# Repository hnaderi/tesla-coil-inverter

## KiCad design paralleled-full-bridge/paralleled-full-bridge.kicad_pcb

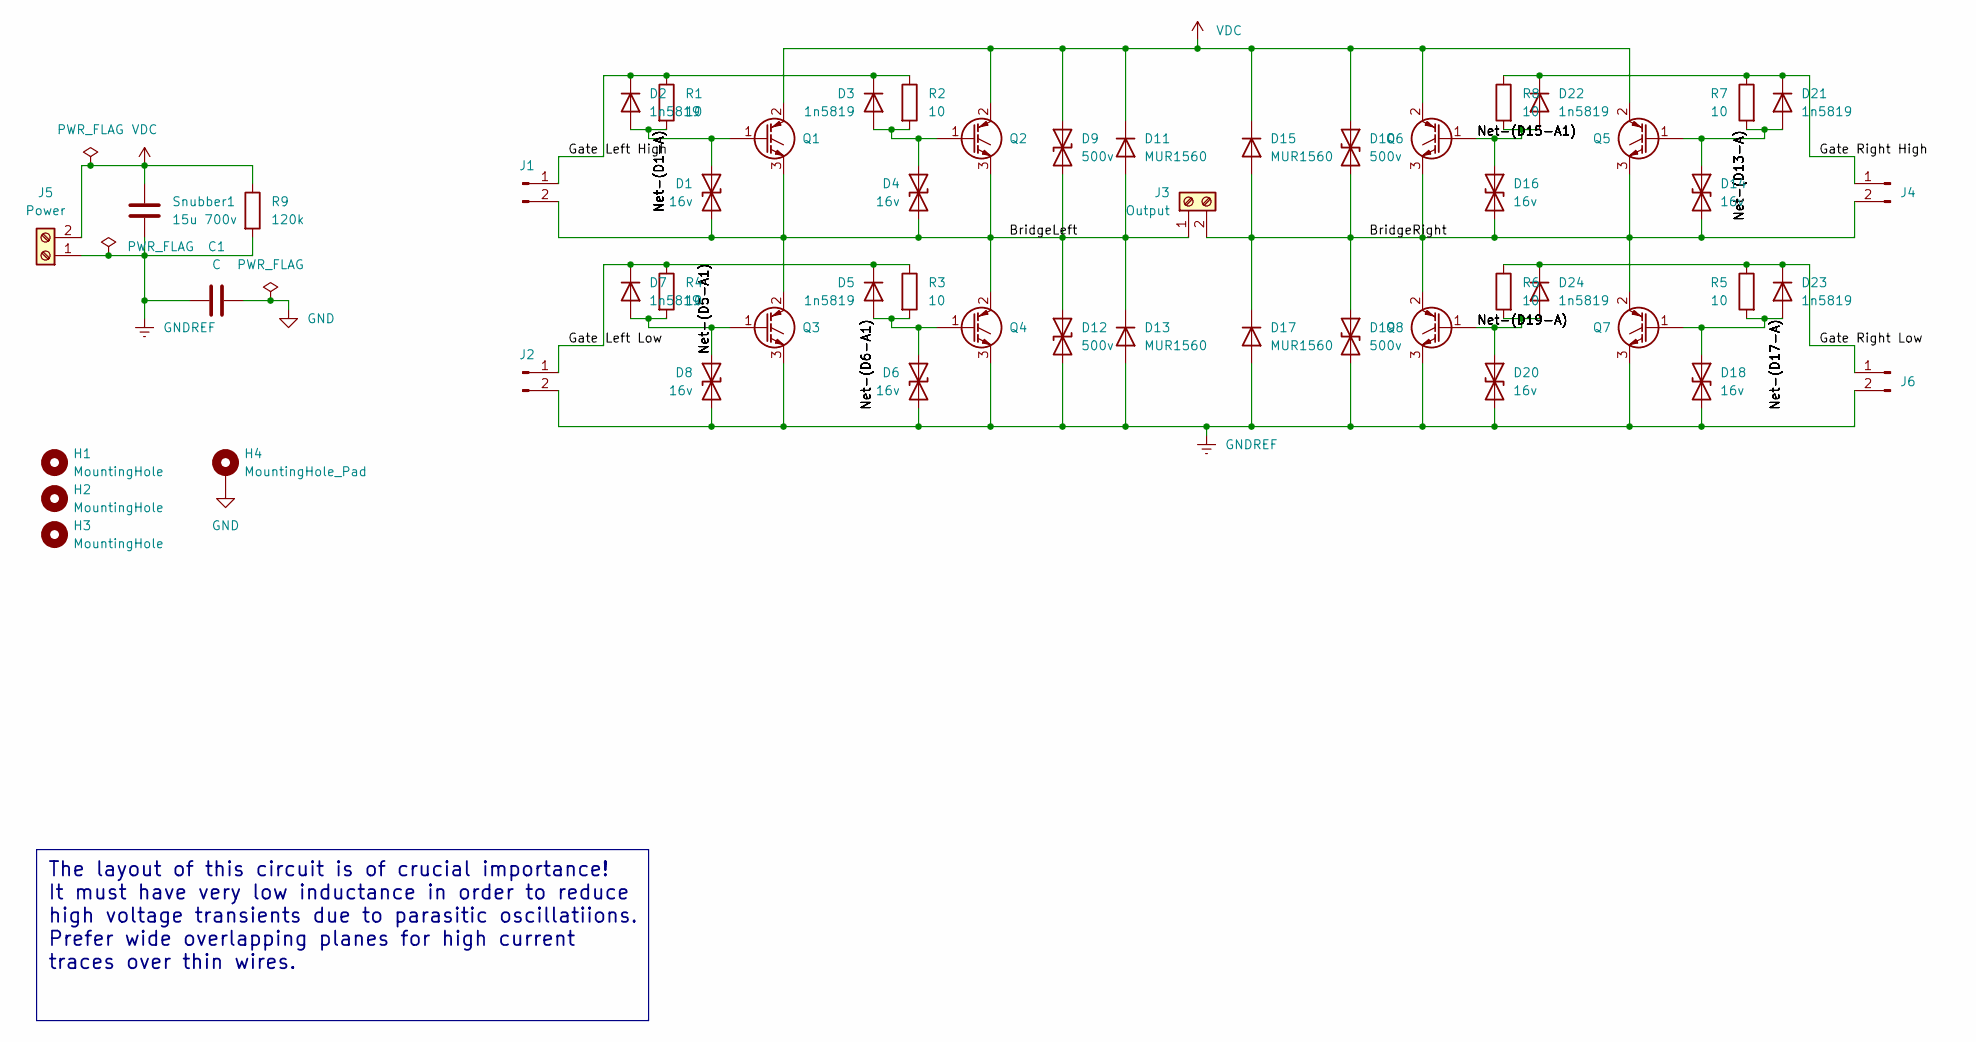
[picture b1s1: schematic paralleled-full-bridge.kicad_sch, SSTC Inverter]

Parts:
C1: C; C_Rect_L26.5mm_W5.0mm_P22.50mm_MKS4
D1, D4, D6, D8, D14, D16, D18, D20: 16v; D_DO-201_P3.81mm_Vertical_KathodeUp
D2, D3, D5, D7, D21, D22, D23, D24: 1n5819; D_DO-41_SOD81_P7.62mm_Horizontal
D9, D10, D12, D19: 500v; D_DO-15_P10.16mm_Horizontal
D11, D13, D15, D17: MUR1560; TO-220-2_Vertical
H1, H2, H3: MountingHole; MountingHole_3.2mm_M3
H4: MountingHole_Pad; MountingHole_3.2mm_M3_DIN965_Pad_TopBottom
J1, J2, J4, J6: Conn_01x02_Pin; JST_XH_B2B-XH-A_1x02_P2.50mm_Vertical
J3: Output; TerminalBlock_bornier-2_P5.08mm
J5: Power; TerminalBlock_bornier-2_P5.08mm
Q1, Q2, Q3, Q4, Q5, Q6, Q7, Q8: Q_NIGBT_GCE; TO-247-3_Vertical
R1, R2, R3, R4, R5, R6, R7, R8: 10; R_Axial_DIN0207_L6.3mm_D2.5mm_P7.62mm_Horizontal
R9: 120k; R_Axial_DIN0516_L15.5mm_D5.0mm_P20.32mm_Horizontal
Snubber1: 15u 700v; C_Rect_L41.5mm_W20.0mm_P37.50mm_MKS4

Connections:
/BridgeLeft: D1.2 (A2), D4.2 (A2), D9.2 (A2), D11.2 (A), D12.1 (A1), D13.1 (K), J1.2, J3.1, Q1.3 (E), Q2.3 (E), Q3.2 (C), Q4.2 (C)
/BridgeRight: D10.2 (A2), D14.2 (A2), D15.2 (A), D16.2 (A2), D17.1 (K), D19.1 (A1), J3.2, J4.2, Q5.3 (E), Q6.3 (E), Q7.2 (C), Q8.2 (C)
/Gate Left High: D2.1 (K), D3.1 (K), J1.1, R1.1, R2.1
/Gate Left Low: D5.1 (K), D7.1 (K), J2.1, R3.1, R4.1
/Gate Right High: D21.1 (K), D22.1 (K), J4.1, R7.1, R8.1
/Gate Right Low: D23.1 (K), D24.1 (K), J6.1, R5.1, R6.1
/Net-(D1-A): D1.1 (A1), D2.2 (A), Q1.1 (G), R1.2
/Net-(D5-A1): D7.2 (A), D8.1 (A1), Q3.1 (G), R4.2
/Net-(D6-A1): D5.2 (A), D6.1 (A1), Q4.1 (G), R3.2
/Net-(D13-A): D14.1 (A1), D21.2 (A), Q5.1 (G), R7.2
/Net-(D15-A1): D16.1 (A1), D22.2 (A), Q6.1 (G), R8.2
/Net-(D17-A): D18.1 (A1), D23.2 (A), Q7.1 (G), R5.2
/Net-(D19-A): D20.1 (A1), D24.2 (A), Q8.1 (G), R6.2
GND: C1.2, H4.1
GNDREF: C1.1, D6.2 (A2), D8.2 (A2), D12.2 (A2), D13.2 (A), D17.2 (A), D18.2 (A2), D19.2 (A2), D20.2 (A2), J2.2, J5.1, J6.2, Q3.3 (E), Q4.3 (E), Q7.3 (E), Q8.3 (E), R9.2, Snubber1.1
unnamed: D3.2 (A), D4.1 (A1), Q2.1 (G), R2.2
VDC: D9.1 (A1), D10.1 (A1), D11.1 (K), D15.1 (K), J5.2, Q1.2 (C), Q2.2 (C), Q5.2 (C), Q6.2 (C), R9.1, Snubber1.2

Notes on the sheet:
The layout of this circuit is of crucial importance! It must have very low inductance in order to reduce high voltage transients due to parasitic oscillatiions. Prefer wide overlapping planes for high current traces over thin wires.

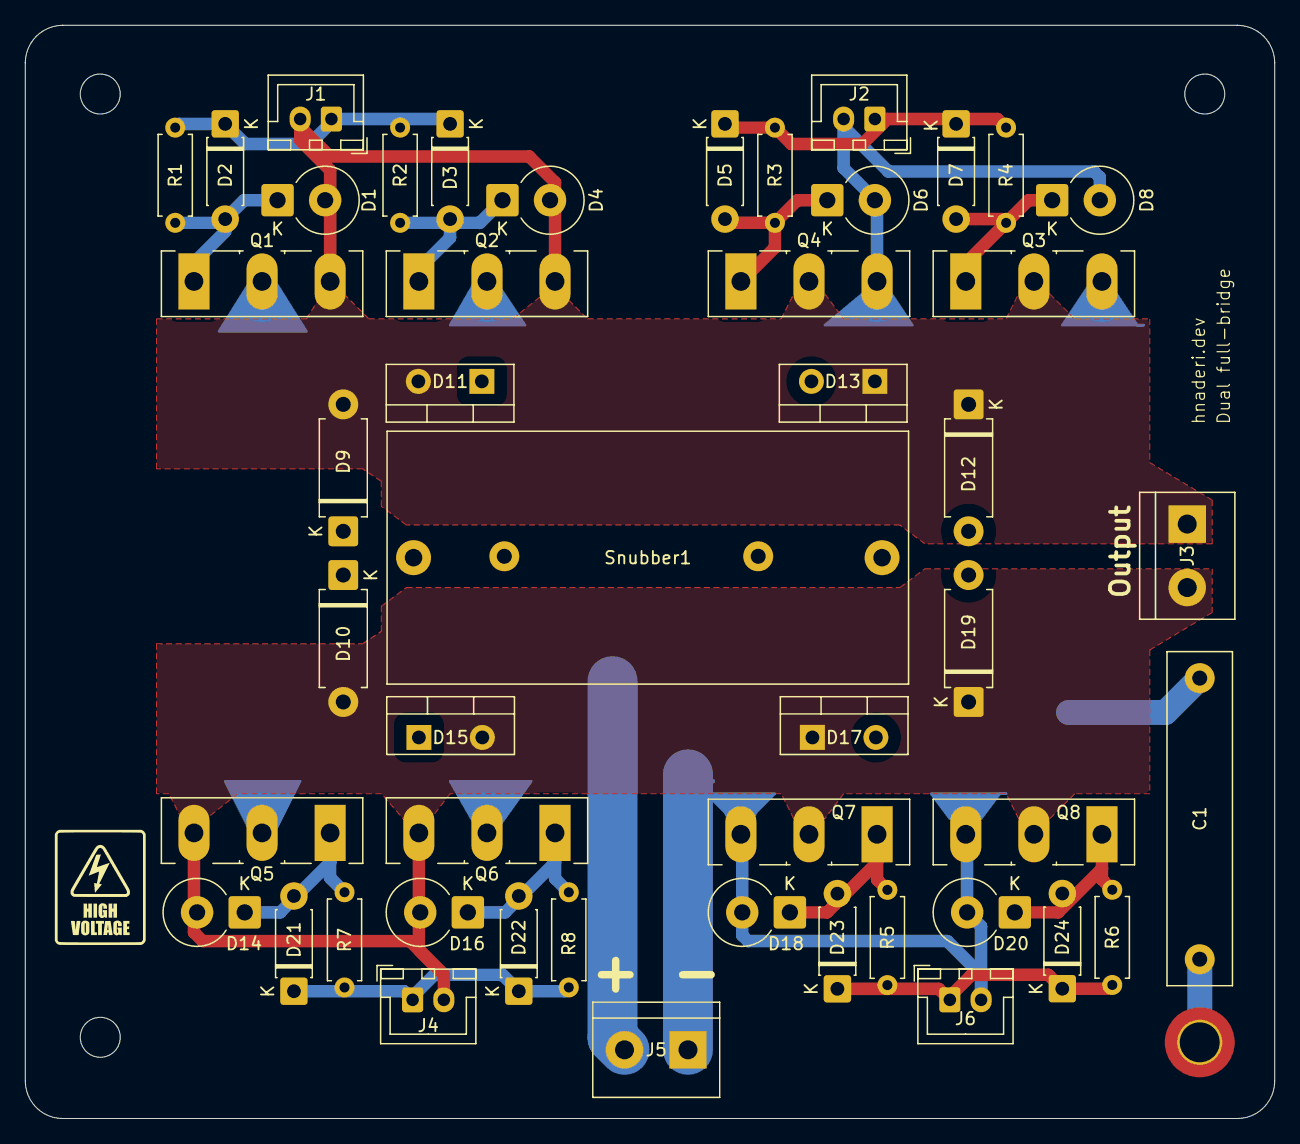
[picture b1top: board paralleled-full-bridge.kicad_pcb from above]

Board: 2 copper layers, 100.0 x 87.5 mm, 53 parts (1 on the bottom side), 17 nets.

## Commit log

2025-07-11 Added paralleled full bridge
2025-07-13 Added fab outputs
